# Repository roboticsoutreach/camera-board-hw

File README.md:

# Hardware design files for the camera module

The Camera Board is a project that aims to find a hardware replacement for webcams.

The current Webcams have a slow shutter speed and the image quality is not great, this means that the robots cannot take images while moving, and can lead to some big issues if the lighting is not right.

Using Raspberry pi camera's we can improve the shutter speed, which will hopefully allow for image processing on the move. We can also have a compute module 3 which deals with all of the image processing so that the robot "brain" doesn't have to. It will also allow for 2 cameras, one which can either be attached to the board directly or over a HDMI cable, and the other will be just over HDMI. This will allow for taking images in different directions, or having a forward facing camera and a turning camera, or could be used for stereo vision.

The first prototype for this board was made at the end of the 2018-2019 academic year, and did not work due to impedance matching issues on the HDMI lines, which meant we could not get a signal out of the Pi. This can likely be fixed by using a 4 layer stackup with a tuned impedance, this way we can ensure that the signal does not destructively interfere with itself in the cable by tuning the width of the PCB traces and the distance between the signals of a differential pair.

The Schematic has currently been updated and is now licenced under CC by SA, where previously it didn't have a license. The next step is to reoute the PCB, and order it so that a second prototype can be tested, if that works, then some of the IO will be removed, and the PCB will be made as small as possible. At this point the PCB will be ready for manufacture.

Once we have a working prototype, work will start on the software which will allow the compute module to do the image processing, and send the data over USB to the "brain" of the computer when requested. The specification and architecture of the software are not yet decided.

This project is currently being led by Joe Morton and Daniel Hobson, so if you would like to get involved with any aspect of this project, please speak to one of us.

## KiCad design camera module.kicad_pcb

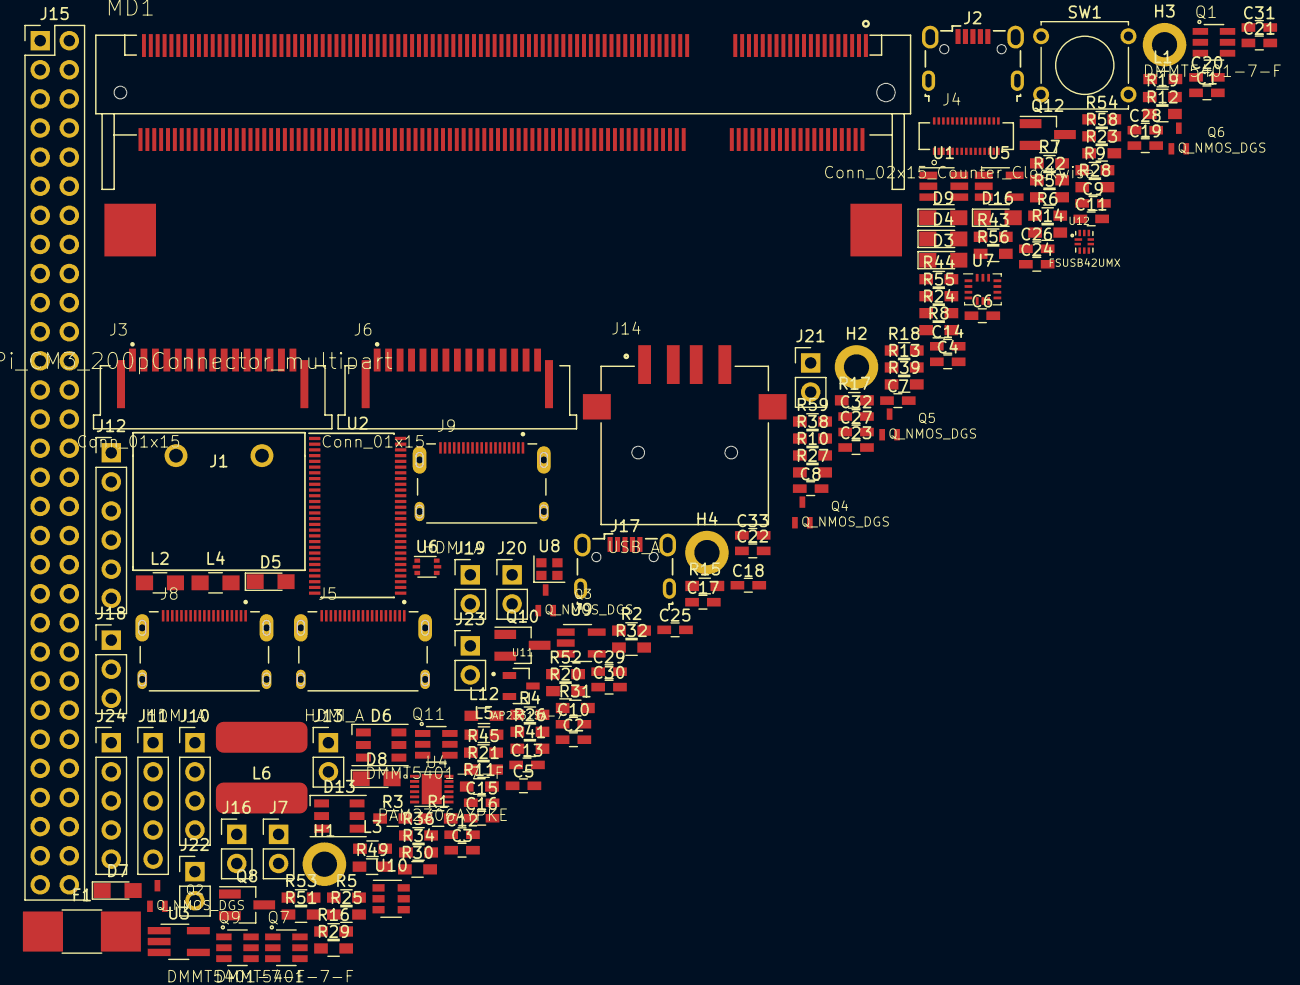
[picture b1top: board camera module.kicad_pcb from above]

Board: 2 copper layers, 154 parts (0 on the bottom side), 158 nets, no tracks yet.

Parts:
C1, C2, C12, C22, C23, C28, C29, C33: 47u; C_0603_HandSoldering
C3, C6, C7, C10, C11, C15, C16, C17, C18, C19, C24, C25, C26, C27, C30: 100n; C_0603_HandSoldering
C4, C5, C13, C14: 10u; C_0603_HandSoldering
C8, C9: NF; C_0603_HandSoldering
C20, C21: 1u; C_0603_HandSoldering
C31: 22u; C_0603_HandSoldering
C32: 100nf; C_0603_HandSoldering
D3, D4, D5, D7, D8, D9, D16: LED; LED_0805_HandSoldering
D6, D13: LED_RGB; LED_RGB_PLCC-6
F1: 2A Polyfuse; L_1812_HandSoldering
H1, H2, H3, H4: MountingHole; MountingHole_2.2mm_M2_DIN965_Pad
J1: Conn_01x02; 7.5mm Camcon
J2: USB_OTG; USB_Micro-B_Wuerth-629105150521
J3, J6: Conn_01x15; AMPHENOL_SFW15R-1STE1LF
J4: Conn_02x15_Counter_Clockwise; HRS_DF37NC-30DS-0.4V(53)
J5, J8, J9: HDMI_A; WURTH_685119136923
J7, J13: Conn_01x02; Pin_Header_Straight_1x02_Pitch2.54mm
J10: Conn_01x04; Pin_Header_Straight_1x04_Pitch2.54mm
J11, J24: Conn_01x05; Pin_Header_Straight_1x05_Pitch2.54mm
J12: Conn_01x06; Pin_Header_Straight_1x06_Pitch2.54mm
J14: USB_A; TE_1-292303-6
J15: Conn_02x30_Odd_Even; Pin_Header_Straight_2x30_Pitch2.54mm
J16, J19, J20, J21, J22, J23: Conn_01x02; Socket_Strip_Straight_1x02_Pitch2.54mm
J17: USB_B_Micro; USB_Micro-B_Wuerth-629105150521
J18: Conn_01x03; Pin_Header_Straight_1x03_Pitch2.54mm
L1, L3, L5: L_Core_Iron; L_0603_HandSoldering
L2, L4: 4.7u; L_0805_HandSoldering
L6: 3.3u; SDR0805
L12: L; L_0603_HandSoldering
MD1: Board_RPi_CM3_200pConnector_multipart; TE_1473149-4
Q1, Q7, Q9, Q11: DMMT5401-7-F; SOT95P285X140-6N
Q2, Q3, Q4, Q5, Q6: Q_NMOS_DGS; SOT323
Q8, Q10, Q12: DMG2305UX; SOT-23_Handsoldering
R1, R4, R5, R6, R12, R14, R15, R17, R18, R44, R49: 0R; R_0603_HandSoldering
R2: 100; R_0603_HandSoldering
R3, R31, R34: 100K; R_0603_HandSoldering
R7, R11, R13, R52, R55, R56, R58: 10k; R_0603_HandSoldering
R8, R9, R24: NF; R_0603_HandSoldering
R10, R23, R25, R26, R27, R28, R29, R30, R32, R36, R39, R41, R43: 470R; R_0603_HandSoldering
R16, R22: 100k; R_0603_HandSoldering
R19, R20: 1.75K; R_0603_HandSoldering
R21: 27K; R_0603_HandSoldering
R38, R45, R51: 47K; R_0603_HandSoldering
R53, R57, R59: 47k; R_0603_HandSoldering
R54: 56.2k; R_0603_HandSoldering
SW1: SW_SPST; SW_Tactile_Straight_KSL0Axx1LFTR
U1: TPS563208; SOT-23-6_Handsoldering
U2: FST16233MTDX; TSSOP-56_6.1x14mm_Pitch0.5mm
U3: LTC3406ES5-1.2; TSOT-23-5_HandSoldering
U4: PAM2306AYPKE; SON45P300X300X80-13N
U5: TLV70228_SOT23-5; SOT-23-5_HandSoldering
U6: EM6K34T2CR; SOT-666
U7: LSM6DS3; Bosch_LGA-14_3x2.5mm_Pitch0.5mm
U8: SIT8008AI-73-XXS-33.333333E; Crystal_SMD_2016-4pin_2.0x1.6mm
U9: XC6222B181MR-G; SOT-23-5_HandSoldering
U10: HDMIULC6-4SC6; SOT-23-6
U11: AP2331SA-7; SOT91P240X120-3N
U12: FSUSB42UMX; IC_FSUSB42UMX

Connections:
1V2: C7.1, C18.1, J4.27, L3.2, U3.5
1V8: C8.1, C14.1, J15.12, J15.24, J15.36, J15.48, J21.1, J21.2, L2.2, R4.1, R6.2, R31.1, R34.1
2V8: C15.1, C17.1, J4.21, U5.5
3V3: C9.1, C13.1, C24.1, C30.1, J3.15, J5.15, J6.15, J9.15, J10.1, J11.1, J12.1, J15.8, J15.16, J15.20, J15.28, J15.32, J15.40, J15.44, J15.52, J16.1, J16.2, J18.3, J20.1, J20.2, L1.1, L4.2, L5.1, L12.1, R1.1, R3.1, R5.1, R10.1, R14.2, R15.2, R16.1, R18.2, R24.1, R43.1, R45.1, U7.5, U12.9
3V3F1: C10.1, C11.1, L5.2, U5.1, U9.1
5V: C1.1, C2.1, C4.1, C5.1, C26.2, J15.4, J15.56, J19.1, J19.2, Q1.5, Q7.5, Q8.2, Q10.2, Q11.6, Q12.2, R2.1, R17.2, R44.1, U2.14, U2.43, U4.1, U4.6, U4.7, U11.3
/HSD1+: J17.3, U12.5
/HSD1-: J17.2, U12.4
/HSD2+: J14.3, U12.7
/HSD2-: J14.2, U12.6
CAM0_CK: J15.13, MD1.21, U2.15
CAM0_CN: MD1.144, U2.48
CAM0_CP: MD1.142, U2.45
CAM0_DN0: MD1.138, U2.4
CAM0_DN1: MD1.150, U2.10
CAM0_DP0: MD1.136, U2.1
CAM0_DP1: MD1.148, U2.7
CAM0_IO0: J15.15, MD1.23, U2.51
CAM0_offboard_CK: J3.12, J5.1, U2.41
CAM0_offboard_CN: J3.8, J5.6, U2.9
CAM0_offboard_CP: J3.9, J5.4, U2.12
CAM0_offboard_DN0: J3.2, J5.12, U2.52
CAM0_offboard_DN1: J3.5, J5.9, U2.46
CAM0_offboard_DP0: J3.3, J5.10, U2.55
CAM0_offboard_DP1: J3.6, J5.7
CAM0_offboard_IO0: J3.11, J5.3, U2.6
CAM0_onboard_CLK: J4.24, R13.1, U2.42
CAM0_onboard_CN: J4.5, U2.8
CAM0_onboard_CP: J4.4, U2.11
CAM0_onboard_DN0: J4.8, U2.53
CAM0_onboard_DN1: J4.11, U2.47
CAM0_onboard_DP0: J4.7, U2.56
CAM0_onboard_DP1: J4.10, U2.50
CAM0_onboard_IO0: U2.5, U3.1, U5.3, U9.3
CAM0_onboard_n: MD1.89, R3.2, U2.29, U2.30
CAM1_CK: J6.12, J9.1
CAM1_CLK: J11.2, J15.5
CAM1_CN: J6.8, J9.6, MD1.149
CAM1_CP: J6.9, J9.4, MD1.147
CAM1_DN0: J6.2, J9.12, MD1.161
CAM1_DN1: J6.5, J9.9, MD1.155
CAM1_DP0: J6.3, J9.10, MD1.159
CAM1_DP1: J6.6, J9.7, MD1.153
CAM1_IO0: J6.11, J9.3, J11.3, J15.7
CAM_1V8: C19.2, J4.26, J4.28, R7.2, R11.1, R12.1, U6.2, U6.5, U8.1, U8.4
CD0_SCL: J15.11, MD1.17, U2.54
CD0_SDA: J11.4, J15.9, U2.40
CD0_offboard_SCL: J3.13, J5.13, U2.3
CD0_offboard_SDA: J3.14, J5.14, U2.17
CD0_onboard_SCL: U2.2, U6.3
CD0_onboard_SDA: U2.16, U6.6
CD1_SCL: J6.13, J9.13, J15.3, MD1.5
CD1_SDA: J6.14, J9.14, J15.1, MD1.3
CK+: J8.10, MD1.113
CK-: J8.12, MD1.111
CM_1V8: C12.1, MD1.183, MD1.184, MD1.185, MD1.186, R6.1
CM_3V3: C23.1, MD1.189, MD1.190, MD1.191, MD1.192, MD1.193, MD1.194, R18.1
CM_VBAT: C22.1, MD1.197, MD1.198, MD1.199, MD1.200, R17.1
D0+: J8.7, MD1.119
D0-: J8.9, MD1.117
D1+: J8.4, MD1.125
D1-: J8.6, MD1.123
D2+: J8.1, MD1.131
D2-: J8.3, MD1.129
EMMC_DISABLE_N: MD1.2, Q4.1
EMMC_EN_N_1V8: MD1.90, Q5.2, R34.2
GND: C1.2, C2.2, C3.2, C4.2, C5.2, C6.2, C7.2, C10.2, C11.2, C12.2, C13.2, C14.2, C15.2, C16.2, C17.2, C18.2, C19.1, C20.1, C21.1, C22.2, C23.2, C24.2, C25.1, C26.1, C27.2, C28.2, C29.2, C30.2, C31.2, C33.2, D3.1, D4.1, D5.1, D6.1, D6.2, D6.3, D7.1, D8.1, D9.1, D13.1, D13.2, D13.3, J1.1, J2.5, J2.6, J3.1, J3.4, J3.7, J3.10, J4.3, J4.6, J4.9, J4.12, J4.15, J4.16, J4.19, J4.22, J4.23, J4.25, J5.2, J5.5, J5.8, J5.11, J5.17, J5.SH, J6.1, J6.4, J6.7, J6.10, J8.2, J8.5, J8.8, J8.11, J8.17, J8.SH, J9.2, J9.5, J9.8, J9.11, J9.17, J9.SH, J10.4, J11.5, J12.6, J14.4, J14.5, J15.2, J15.6, J15.10, J15.14, J15.18, J15.22, J15.26, J15.30, J15.34, J15.38, J15.42, J15.46, J15.50, J15.54, J15.58, J15.60, J17.5, J17.6, J18.1, J22.1, J22.2, J23.1, MD1.1, MD1.7, MD1.8, MD1.13, MD1.14, MD1.19, MD1.20, MD1.25, MD1.26, MD1.31, MD1.32, MD1.37, MD1.38, MD1.43, MD1.44, MD1.49, MD1.50, MD1.55, MD1.56, MD1.61, MD1.62, MD1.67, MD1.68, MD1.73, MD1.74, MD1.79, MD1.80, MD1.85, MD1.86, MD1.91, MD1.92, MD1.97, MD1.98, MD1.103, MD1.104, MD1.109, MD1.110, MD1.115, MD1.116, MD1.121, MD1.122, MD1.127, MD1.133, MD1.134, MD1.139, MD1.140, MD1.145, MD1.146, MD1.151, MD1.152, MD1.157, MD1.163, MD1.164, MD1.169, MD1.170, MD1.181, MD1.182, MD1.187, MD1.188, MD1.195, MD1.196, Q3.3, Q5.3, Q6.3, R8.2, R9.2, R22.2, R38.2, R51.2, R52.2, R53.2, R55.2, R56.2, R57.2, R58.2, R59.2, U1.1, U2.13, U2.27, U2.28, U2.44, U3.2, U4.3, U4.9, U4.13, U5.2, U7.2, U7.3, U7.6, U7.7, U8.2, U9.2, U10.2, U11.1, U12.3, U12.8
GPIO0-27_VREF: C20.2, MD1.39, MD1.40, R14.1
GPIO12: J15.25, MD1.45
GPIO13: J15.27, MD1.47
GPIO14_TX: J10.2, J15.29, MD1.51
GPIO15_RX: J10.3, J15.31, MD1.53
GPIO16: J15.33, J24.1, MD1.57
GPIO17: J15.35, J24.2, MD1.59
GPIO18: J15.37, J24.3, MD1.63
GPIO19: J15.39, J24.4, MD1.65
GPIO20: J15.41, J24.5, MD1.69
GPIO21: J15.43, MD1.71
GPIO22: J15.45, MD1.75
GPIO23: J15.47, MD1.77
GPIO24: J15.49, MD1.81
GPIO25: J15.51, MD1.83
GPIO26: J15.53, MD1.87
GPIO28: MD1.28, R23.1
GPIO28-45_VREF: C21.2, MD1.41, MD1.42, R15.1
GPIO29: MD1.30, R26.1
GPIO30: MD1.34, R28.1
GPIO31: MD1.36, R30.1
GPIO32: MD1.46, R32.1
GPIO38: MD1.64, R25.1
GPIO39: MD1.66, R27.1
GPIO40: MD1.70, R29.1
GPIO41: MD1.72, R36.1
GPIO42: MD1.76, R39.1
GPIO43: MD1.78, R41.1
H5V: C27.1, J8.18, Q2.2, R19.1, R20.1, R21.1, U10.5, U11.2
HDMI_CEC: MD1.171, Q2.1, R24.2
HDMI_HPD: J8.19, Q3.2, R22.1, U10.4
HDMI_HPD_N_1V8: MD1.88, Q3.1, R31.2
HDMI_SCL: J8.15, MD1.175, R20.2, U10.3
HDMI_SDA: J8.16, MD1.173, R19.2, U10.1
unnamed: C3.1, R2.2, U4.12
unnamed: C6.1, L1.2, U3.4
unnamed: C8.2, R4.2, R8.1, U4.10
unnamed: C9.2, R5.2, R9.1, U4.4
unnamed: C16.1, R12.2, U9.5
unnamed: C25.2, L12.2, U7.8
unnamed: C31.1, J1.2, U1.3, U1.5
unnamed: C32.1, L6.1, U1.2
unnamed: C32.2, U1.6
unnamed: C33.1, L6.2, Q7.6, Q10.3, R54.1
unnamed: D3.2, R10.2
unnamed: D4.2, R23.2
unnamed: D5.2, R26.2
unnamed: D6.4, R29.2
unnamed: D6.5, R27.2
unnamed: D6.6, R25.2
unnamed: D7.2, R28.2
unnamed: D8.2, R30.2
unnamed: D9.2, R32.2
unnamed: D13.4, R41.2
unnamed: D13.5, R39.2
unnamed: D13.6, R36.2
unnamed: D16.1, Q4.3, Q5.1
unnamed: D16.2, R43.2
unnamed: F1.1, Q1.6, Q8.3
unnamed: F1.2, J2.1
unnamed: J4.1, R11.2, U6.4
unnamed: J4.2, R7.1, U6.1
unnamed: J7.1, U7.4
unnamed: J7.2, U7.9
unnamed: J8.13, Q2.3, R21.2, U10.6
unnamed: J13.1, R49.2
unnamed: J13.2, Q9.6, Q12.3
unnamed: L2.1, U4.2
unnamed: L3.1, U3.3
unnamed: L4.1, U4.8
unnamed: MD1.4, MD1.6, R1.2
unnamed: Q1.1, Q1.2, Q1.3, R52.1
unnamed: Q1.4, Q8.1, R53.1
unnamed: Q4.2, R38.1, SW1.2
unnamed: Q6.1, R45.2, U12.10
unnamed: Q7.1, Q7.2, Q7.3, R56.1
unnamed: Q7.4, Q10.1, R57.1
unnamed: Q11.1, Q12.1, R59.1
unnamed: Q9.1, Q9.2, Q11.2, R58.1
unnamed: R13.2, U8.3
unnamed: R54.2, R55.1, U1.4
RUN: J15.57, J23.2, MD1.177
SPI0_CLK: J12.5, J15.23, MD1.35, U7.13
SPI0_CS: J12.2, J15.17, MD1.27, R16.2, U7.12
SPI0_MISO: J12.3, J15.19, MD1.29, U7.1
SPI0_MOSI: J12.4, J15.21, MD1.33, U7.14
USB_DM: MD1.167, U12.2
USB_DP: MD1.165, U12.1
USB_OTGID: J17.4, J18.2, MD1.168
VBUSA: C28.1, C29.1, J14.1, R44.2
VBUSB: J17.1, Q6.2, R49.1, R51.1, SW1.1

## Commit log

2019-02-12 Added .gitignore and readme
2019-02-18 My first commit, I hope I didn't screw stuff up
2019-02-18 Joe crashed KiCAD, not my fault
2019-02-20 Tweaks to routing, 4th mounting hole added, DRC issues fixed
2019-02-25 Via for GND on mux moved, ready for checking
2019-03-11 Final files. As sent to manufacture
2019-03-15 Added some vias to replace plated slots, removed a couple of stray tracks
2019-03-18 Added missing outline on edgecuts layer(!)
2019-03-25 Added BOM, started ticking off parts that arrived
2019-03-26 BOM checked against recieved parts and ommisions noted
2019-05-01 update BOM, now finished
2019-05-01 Remove windows file paths in symbol libraries
2019-08-26 Update .gitignore
    Pulls in changes that have been made to the standard .gitignore
    file for KiCad projects [1] since this repository was created.
    Details of these changes can be found in the changelog for
    this file [2].
    Closes #1.
    [1]: https://github.com/github/gitignore/blob/0455041ec4bab7b8835842e0a6d8b67e8446beeb/KiCad.gitignore
2019-09-17 License under CC_BY-SA 4.0
    Closes #6
2019-09-24 fixing library structure
2019-09-24 Uploaded the start of V1
    libraries are now compliant with license, and schematic has been slightly changed to be cheaper, MOSFET footprints also fixed
2019-09-24 updated to match kb
2019-11-27 Starting new version
    Updated GPIO, added EEPROM and added overvoltage protection
2019-12-05 A few small changes and fixes
2020-02-10 V1 routed ready for review
